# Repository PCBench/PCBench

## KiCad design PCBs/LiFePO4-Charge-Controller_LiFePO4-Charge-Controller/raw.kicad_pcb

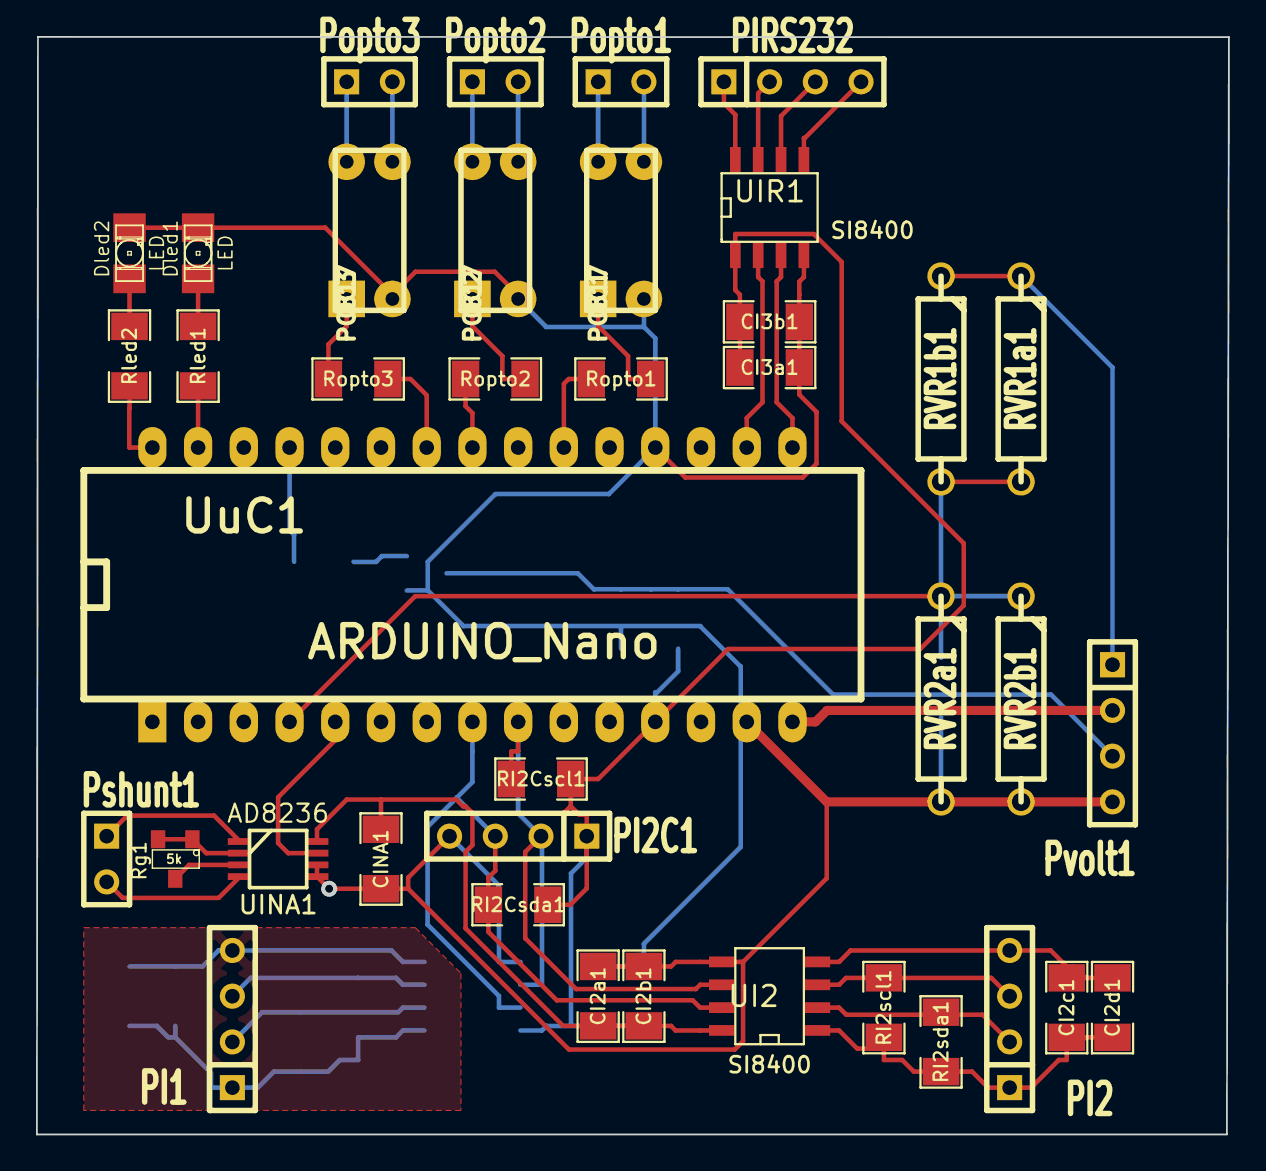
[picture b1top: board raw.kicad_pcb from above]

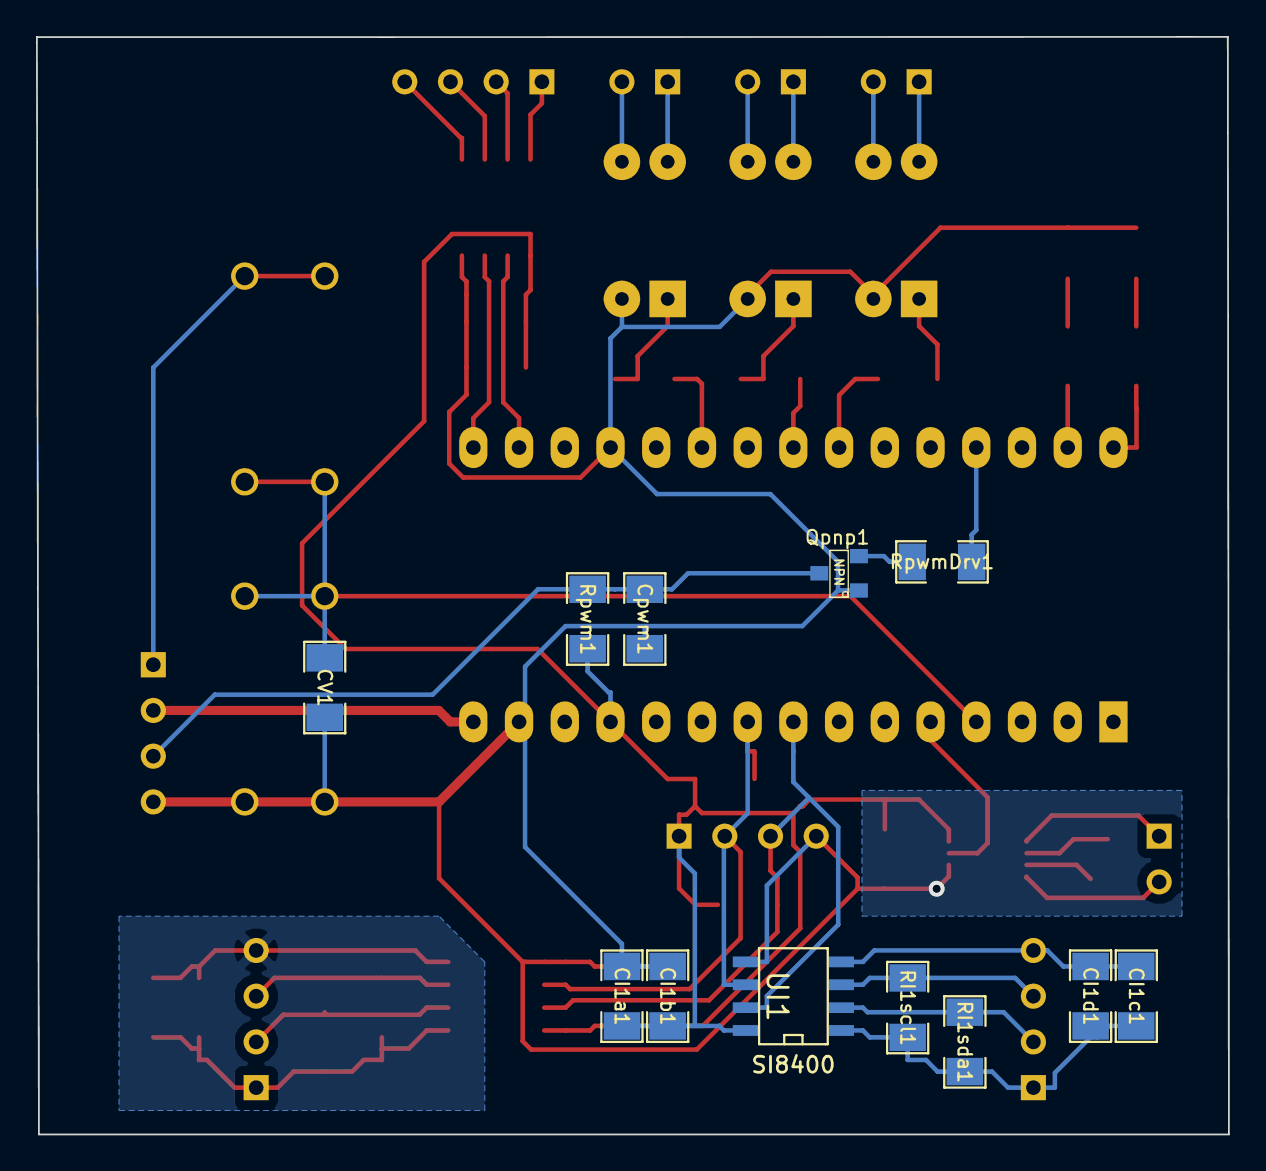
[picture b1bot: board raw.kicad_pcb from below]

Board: 2 copper layers, 66.2 x 61.0 mm, 51 parts (12 on the bottom side), 45 nets.

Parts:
CI1a1, CI1c1, CI2a1, CI2c1, CI3a1: 100nF; SM1206
CI1b1, CI1d1, CI2b1, CI2d1, CI3b1: 1uF; SM1206
CINA1: 100nF; SM1206
CV1: 10pF; SM1206
Cpwm1: 300nF; SM1206
Dled1, Dled2: LED; LED-1206
OC1, OC2, OC3: PC817; DIP-4
PI1, PI2, PI2C1: I2C; SIL-4
PIRS232: RS232; SIL-4
Popto1, Popto2, Popto3: opto; SIL-2
Pshunt1: differential; SIL-2
Pvolt1: Gnd PWM 12V B+; SIL-4
Qpnp1: NPN; SOT23
RI1scl1, RI1sda1, RI2scl1, RI2sda1: 5k; SM1206
RI2Cscl1, RI2Csda1: 1.8k; SM1206
RVR1a1, RVR1b1: 99k; R4-5
RVR2a1, RVR2b1: 1k; R4-5
Rg1: 5k; SOT23
Rled1: 1k; SM1206
Rled2: 1K; SM1206
Ropto1, Ropto2, Ropto3: 1k; SM1206
Rpwm1: 120; SM1206
RpwmDrv1: 560; SM1206
UI1, UI2: SI8400; SO8E
UINA1: AD8236; MSOP_8
UIR1: SI8400; SO8E
UuC1: ARDUINO_Nano; arduino_mini

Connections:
5v: CI1a1.1, CI1b1.1, CI2a1.1, CI2b1.1, CI3a1.2, CI3b1.2, CINA1.1, PI2C1.1, RI2Cscl1.1, RI2Csda1.1, Rpwm1.2, UI1.8, UI2.8, UINA1.8, UIR1.1, UuC1.12
D3: Ropto1.1, UuC1.21
D5: Ropto2.1, UuC1.23
D6: Ropto3.1, UuC1.24
Gnd: CI1a1.2, CI1b1.2, CI2a1.2, CI2b1.2, CI3a1.1, CI3b1.1, CINA1.2, CV1.2, Cpwm1.2, Dled1.2, Dled2.2, OC1.2, OC2.2, OC3.2, PI2C1.4, Pvolt1.4, Qpnp1.1, RVR2a1.2, RVR2b1.2, UI1.5, UI2.5, UINA1.5, UINA1.6, UIR1.4, UuC1.14, UuC1.19
I2C1_GND: CI1c1.2, CI1d1.2, PI1.4, UI1.4
I2C2_GND: CI2c1.2, CI2d1.2, PI2.4, UI2.4
unnamed: UIR1.2, UuC1.17
unnamed: UIR1.3, UuC1.16
unnamed: PI1.3, RI1scl1.2, UI1.3
unnamed: PI1.2, RI1sda1.2, UI1.2
unnamed: PI2.2, RI2sda1.2, UI2.2
unnamed: CV1.1, RVR1a1.2, RVR1b1.2, RVR2a1.1, RVR2b1.1, UuC1.4
unnamed: PIRS232.3, UIR1.6
unnamed: PIRS232.2, UIR1.7
unnamed: PIRS232.1, UIR1.8
unnamed: PI2.3, RI2scl1.2, UI2.3
unnamed: OC1.4, Popto1.1
unnamed: OC3.4, Popto3.1
unnamed: OC3.1, Ropto3.2
unnamed: OC2.3, Popto2.2
unnamed: OC2.4, Popto2.1
unnamed: OC2.1, Ropto2.2
unnamed: OC1.3, Popto1.2
unnamed: OC3.3, Popto3.2
unnamed: OC1.1, Ropto1.2
unnamed: Cpwm1.1, Pvolt1.3, Qpnp1.3, Rpwm1.1
unnamed: Qpnp1.2, RpwmDrv1.2
unnamed: Dled1.1, Rled1.2
unnamed: Dled2.1, Rled2.2
unnamed: RpwmDrv1.1, UuC1.27
unnamed: Rled2.1, UuC1.30
unnamed: Rled1.1, UuC1.29
unnamed: Rg1.1, Rg1.2, UINA1.2
unnamed: UINA1.7, UuC1.5
unnamed: Pshunt1.2, UINA1.4
unnamed: Pshunt1.1, UINA1.1
unnamed: Rg1.3, UINA1.3
unnamed: Pvolt1.2, UuC1.15
unnamed: CI2c1.1, CI2d1.1, PI2.1, RI2scl1.1, RI2sda1.1, UI2.1
unnamed: CI1c1.1, CI1d1.1, PI1.1, RI1scl1.1, RI1sda1.1, UI1.1
unnamed: PI2C1.3, RI2Csda1.2, UI1.7, UI2.7, UuC1.8
unnamed: PI2C1.2, RI2Cscl1.2, UI1.6, UI2.6, UuC1.9
unnamed: Pvolt1.1, RVR1a1.1, RVR1b1.1
RS232_GND: PIRS232.4, UIR1.5

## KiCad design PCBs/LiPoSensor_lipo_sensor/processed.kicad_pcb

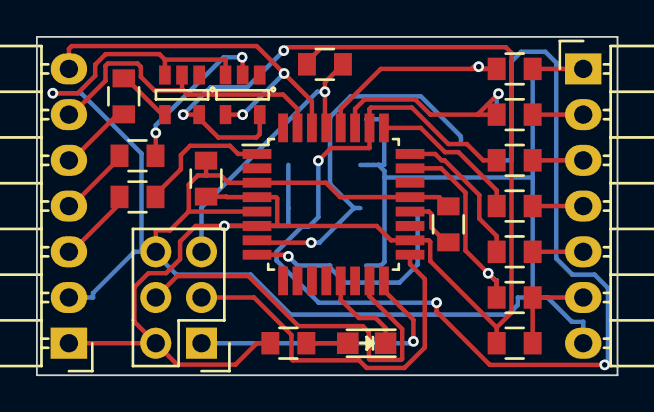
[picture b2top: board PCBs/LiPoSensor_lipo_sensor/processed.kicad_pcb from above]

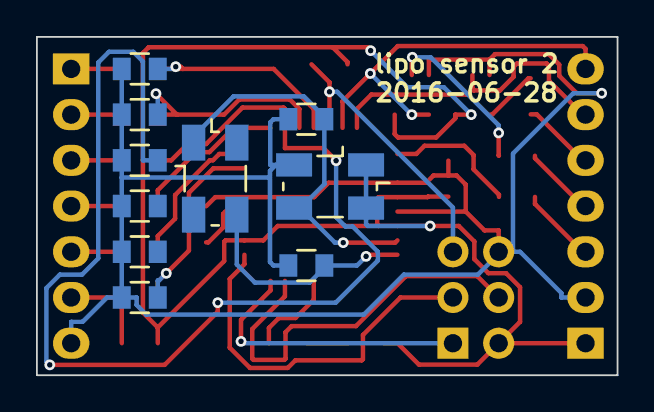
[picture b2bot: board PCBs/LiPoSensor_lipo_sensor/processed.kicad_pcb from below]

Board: 2 copper layers, 32.3 x 18.8 mm, 31 parts (10 on the bottom side), 31 nets.

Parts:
5k1: 4k7; C_0805
C1, C3: 100nF; C_0805
C2, C5: 22pF; C_0805
D1: LED; LED_0805
IC1: ATMEGA328P-A; TQFP-32_7x7mm_Pitch0.8mm
P1: CONN_02X03; Pin_Header_Straight_2x03
P2, P3: CONN_01X07; Pin_Header_Angled_1x07
P4: OSZILLATOR; Oszillator_SMD_5032_4Pads
P5, P6: INVERTER; SOT-23-5
P7: QUARZ; Oszillator_SMD_5032_4Pads
R1: 680; C_0805
R2, R5, R9: 22k; C_0805
R3, R6: 1k; C_0805
R4: 0; C_0805
R7: 18k; C_0805
R8: 1k2; C_0805
R10: 1k8; C_0805
R11: 15k; C_0805
R12: 2k2; C_0805
R13: 12k; C_0805
R14: 3k9; C_0805
R15, R17: R; C_0805
R16: 10k; C_0805

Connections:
/Cell1: IC1.23, R13.2, R14.1
/Cell2: IC1.24, R11.2, R12.1
/Cell3: IC1.25, R9.2, R10.1
/Cell4: IC1.26, R7.2, R8.1
/Cell5: IC1.27, R5.2, R6.1
/Cell6: IC1.28, R2.2, R3.1
/LED: D1.1, IC1.13
/RX: IC1.30, P2.7, P6.4
/S.Port: 5k1.2, IC1.1
/TX: IC1.31, P2.6, P5.2
GND: C1.2, C2.1, C3.1, C5.1, IC1.3, IC1.5, IC1.21, P1.6, P2.2, P3.7, P4.2, P5.3, P6.3, R3.2, R6.2, R8.2, R10.2, R12.2, R14.2
unnamed: 5k1.1, P2.3
unnamed: C2.2, IC1.7, P4.3, P7.1
unnamed: C3.2, IC1.20
unnamed: C5.2, IC1.8, P7.3
unnamed: D1.2, R1.2
unnamed: IC1.15, P1.4
unnamed: IC1.16, P1.1
unnamed: IC1.17, P1.3
unnamed: IC1.29, P1.5, R16.2
unnamed: P2.4, R17.2
unnamed: P2.5, R15.2
unnamed: P3.1, R2.1
unnamed: P3.2, R5.1
unnamed: P3.3, R7.1
unnamed: P3.4, R9.1
unnamed: P3.5, R11.1
unnamed: P3.6, R4.2, R13.1
unnamed: P5.4, R15.1
unnamed: P6.2, R17.1
VCC: C1.1, IC1.4, IC1.6, IC1.18, P1.2, P2.1, P4.1, P4.4, P5.5, P6.5, R1.1, R4.1, R16.1

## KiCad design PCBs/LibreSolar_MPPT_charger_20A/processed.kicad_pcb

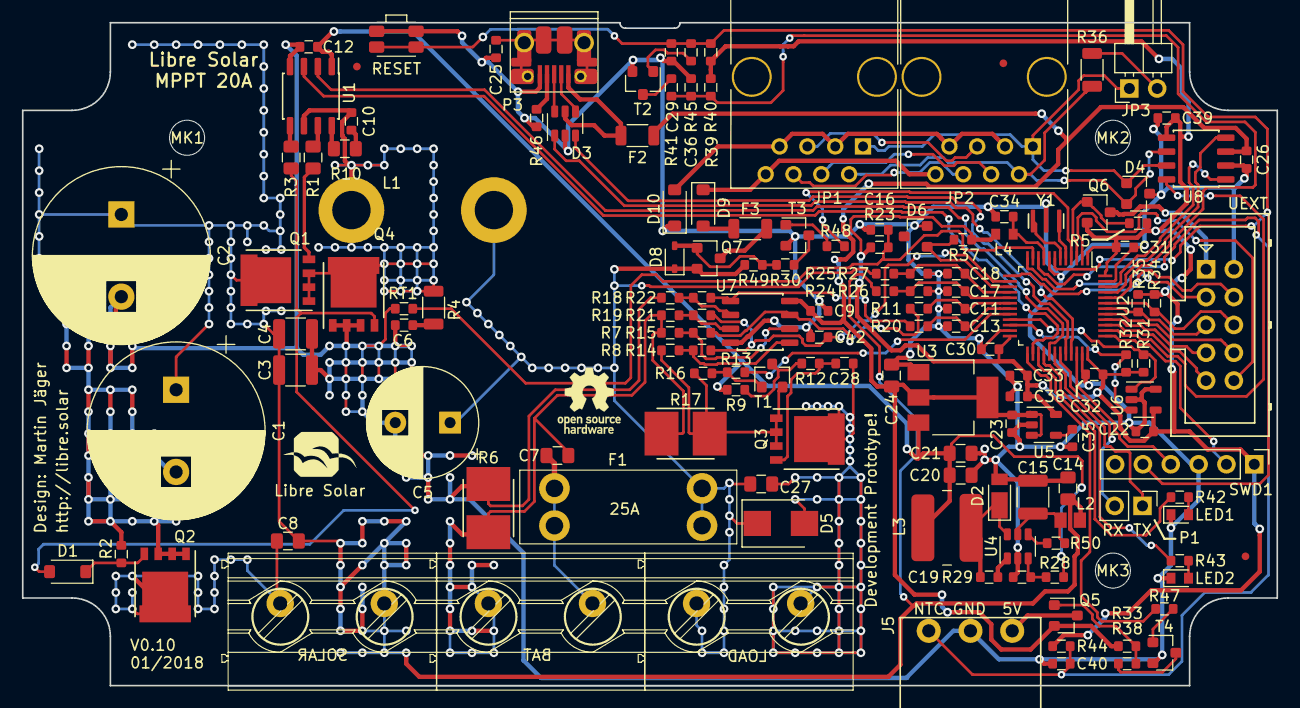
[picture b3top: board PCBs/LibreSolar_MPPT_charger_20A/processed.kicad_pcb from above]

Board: 2 copper layers, 114.5 x 60.5 mm, 146 parts (0 on the bottom side), 102 nets.

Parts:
C1, C2: 1000u; CP_Radial_D16.0mm_P7.50mm
C3, C4, C15: 4.7u; C_1210_3225
C5: 820u; CP_Radial_D10.0mm_P5.00mm
C6: 1n; C_0603_1608
C7, C8, C14, C27: 1u; C_0805_2012
C9, C10, C16, C19, C22, C25, C26, C29, C30, C31, C32, C34, C39, C40, C42: 100n; C_0603_1608
C11, C13, C17, C18, C28: 10n; C_0603_1608
C12, C23, C33, C36, C38: 2.2u; C_0603_1608
C20, C21, C24: 10u; C_0805_2012
C35: 100p; C_0603_1608
D1, D9, D10: 1N4148; D_SOD-123
D2: SS16FP; D_PowerDI-123
D3: USBLC6-2SC6Y; SOT-23-6
D4: NUP2105L; SOT-23
D5: SMBJ36A; D_SMB
D6: LM4040CYM3-2.5; SOT-23
D8: MM3Z12VT1G; D_SOD-323
F1: 25A; KEYSTONE-FUSE-3557-2
F2, F3: 200mA; R_1206_3216
J1: SOLAR; Phoenix_Contact_MKDS_5-2-952
J2: LOAD; Phoenix_Contact_MKDS_5-2-952
J3: BAT; Phoenix_Contact_MKDS_5-2-952
J4: UEXT; Box_Header_2x05x2.54mm_Straight
J5: CONN_01X03; Phoenix_Contact_MC_1,5_3-G-3,81
JP1, JP2: RJ45_NS; RJ45_8P8C
JP3: Jumper_NC_Small; PinHeader_1x02_P2.54mm_Horizontal
L1: 22uH; L-FERYSTER-DTMSS-27
L2: 4.7uH; L_0805_2012Metric
L3: 47uH; Bourns_SRN6045TA
L4: 600R; L_0603_1608Metric
LED1: LED_red; LED_0603_1608Metric
LED2: LED_green; LED_0603_1608Metric
LOGO1: LIBRE_SOLAR; LIBRESOLAR_LOGO
LOGO2: OPEN_HARDWARE; OSHW-Logo_5.7x6mm_SilkScreen
MK1, MK2, MK3: Mounting_Hole; MountingHole_3.2mm_M3
P1: CONN_01X02; PinHeader_1x02_P2.54mm_Vertical
P3: USB Micro B; USB_Micro-B_10103594-0001LF
Q1, Q2, Q3, Q4: CSD18540Q5B; 5X6_MOSFET
Q5, Q6, Q7: BSS84; SOT-23
R1, R3, R10: 3.3; R_0805_2012
R2, R39, R40, R50: 1M; R_0603_1608
R4: 2.2; R_1206_3216
R5, R24, R25, R33, R46, R47: 100k; R_0603_1608
R6, R17: 2m; R_Bourns_CRE2512
R7, R8, R11, R12, R13, R18, R19, R20, R31, R32, R34, R35, R38, R41: 2.2k; R_0603_1608
R9, R30, R45, R49: 56k; R_0603_1608
R14, R15, R21, R22: 150k; R_0603_1608
R16, R23, R27, R29, R37, R44, R48: 10k; R_0603_1608
R26: 5.6k; R_0603_1608
R28: 110k; R_0603_1608
R36: 120; R_1206_3216
R42, R43: 330; R_0603_1608
RT1: 10k; R_0603_1608
SW1: SW_PUSH; SW_SPST_EVQP7A
SWD1: ST_Nucleo_SWD; PinHeader_1x06_P2.54mm_Vertical
T1, T2, T3, T4: MMBT3904; SOT-23
U1: LM5107; SOIC-8_3.9x4.9mm_Pitch1.27mm
U2: STM32F072CB; LQFP-48_7x7mm_P0.5mm
U3: AZ1117; SOT-223-3_TabPin2
U4: MP2459; SOT-23-6
U5: AP2210-3.3; SOT-23-5
U6: 24AA01; SOT-23-5
U7: LM258; SOIC-8_3.9x4.9mm_Pitch1.27mm
U8: TJA1042T/3; SOIC-8_3.9x4.9mm_Pitch1.27mm
Y1: 8MHz; Resonator_Murata_CSTCE_G

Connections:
+3V3: C22.1, C30.1, C31.1, C32.1, C33.1, C38.1, C39.1, L4.1, Q6.2, R5.1, R23.1, R31.2, R32.2, R34.2, R35.2, R37.2, R39.2, R40.2, R44.1, SWD1.1, U2.1, U2.24, U2.36, U2.48, U5.5, U6.4, U8.5
+5V: C9.1, C23.1, C24.1, C26.1, F2.1, Q5.2, R33.1, U3.2, U5.1, U5.3, U7.8, U8.3
+10V: C12.1, C20.1, C21.1, L3.2, R9.2, R28.1, U1.1, U3.3
/Analog Frontend/TEMP_BAT: C40.1, J5.1, R44.2, U2.10
/Analog Frontend/TEMP_INT: C16.1, R23.2, RT1.1, U2.11
/Communication Interfaces/5V_OUT: J5.3, Q5.3
/Communication Interfaces/5V_OUT_EN: R47.2, U2.25
/Communication Interfaces/CAN_GND: D10.2, JP1.3, JP1.7, JP2.3, JP2.7
/Communication Interfaces/CAN_H: D4.1, JP1.1, JP2.1, JP3.1, U8.7
/Communication Interfaces/CAN_L: D4.2, JP1.2, JP2.2, R36.2, U8.6
/Communication Interfaces/CAN_RX: U2.45, U8.4
/Communication Interfaces/CAN_SHLD: JP1.6, JP2.6
/Communication Interfaces/CAN_STB: U2.38, U8.8
/Communication Interfaces/CAN_TX: U2.46, U8.1
/Communication Interfaces/CAN_V+: D9.1, JP1.8, JP2.8
/Communication Interfaces/RJ45_4: JP1.4, JP2.4
/Communication Interfaces/RJ45_5: JP1.5, JP2.5
/Communication Interfaces/UEXT_EN: Q6.1, R5.2, U2.3
/Communication Interfaces/UEXT_RX: J4.4, U2.13
/Communication Interfaces/UEXT_TX: J4.3, U2.12
/Communication Interfaces/USB_DM: D3.3, U2.32
/Communication Interfaces/USB_DP: D3.1, U2.33
/Communication Interfaces/V_BUS_EN: R48.2, U2.4
/DCDC power stage/BAT+: C7.1, F1.2, J3.2
/DCDC power stage/BAT-: C7.2, J3.1, R6.2, R7.2, R17.1, R19.2
/DCDC power stage/DCDC_IN: C1.1, C2.1, C3.1, C4.1, C8.1, C14.1, J1.2, L2.1, Q1.D, R24.1
/DCDC power stage/HS_DRV: R1.2, U1.7
/DCDC power stage/LOAD-: C27.2, C28.2, D5.2, J2.2, Q3.D
/DCDC power stage/LOAD-SW: Q3.S, R8.2, R16.1, R17.2, T1.2
/DCDC power stage/LS_DRV: R3.2, U1.5
/DCDC power stage/PWM_HS: U1.2, U2.29
/DCDC power stage/PWM_LS: U1.3, U2.26
/DCDC power stage/SOLAR-: C8.2, J1.1, Q2.D
/DCDC power stage/SW_NODE: C10.2, L1.1, Q1.S, Q4.D, R4.2, U1.6
/DCDC power stage/~LOAD_EN: R13.2, U2.20
/DCDC_OUT: C5.1, C27.1, D5.1, D8.1, F1.1, J2.1, L1.2, Q7.2, R25.1, R49.1
/MCU/BOOT0: C36.1, R39.1, R41.2, U2.44
/MCU/DAC: C42.1, R14.1, R21.2, U2.14
/MCU/I2C1_SCL: J4.5, R35.1, U2.42
/MCU/I2C1_SDA: J4.6, R34.1, U2.43
/MCU/I2C2_SCL: R31.1, U2.21, U6.1
/MCU/I2C2_SDA: R32.1, U2.22, U6.3
/MCU/I_DCDC: C13.1, R20.2, U2.19
/MCU/I_LOAD: C11.1, R11.2, U2.18
/MCU/LED1: R42.2, U2.27
/MCU/LED2: R43.2, U2.28
/MCU/OSC_IN: U2.5, Y1.1
/MCU/OSC_OUT: U2.6, Y1.3
/MCU/SPI1_MISO: J4.7, U2.40
/MCU/SPI1_MOSI: J4.8, U2.41
/MCU/SPI1_SCK: J4.9, U2.39
/MCU/SSEL: J4.10, U2.2
/MCU/SWCLK: SWD1.2, U2.37
/MCU/SWDIO: SWD1.4, U2.34
/MCU/USART1_RX: P1.2, U2.31
/MCU/USART1_TX: P1.1, U2.30
/MCU/V_BAT: C18.1, R25.2, R27.1, U2.16
/MCU/V_REF: D6.1, R37.1, U2.15
/MCU/V_SOLAR: C17.1, R24.2, R26.1, U2.17
/MCU/~RESET: C29.1, R40.1, R45.1, SW1.1, SWD1.5, U2.7
GND: C1.2, C2.2, C3.2, C4.2, C5.2, C6.2, C9.2, C11.2, C12.2, C13.2, C14.2, C15.2, C16.2, C17.2, C18.2, C20.2, C21.2, C22.2, C23.2, C24.2, C25.2, C26.2, C29.2, C30.2, C31.2, C32.2, C33.2, C34.2, C35.2, C36.2, C38.2, C39.2, C40.2, C42.2, D2.2, D3.2, D4.3, D6.2, D10.1, J4.2, J5.2, LED1.1, LED2.1, P3.5, Q2.S, Q4.S, R2.1, R6.1, R18.2, R26.2, R27.2, R29.2, R46.2, RT1.2, SW1.2, SWD1.3, T2.2, T3.2, T4.2, U1.4, U2.8, U2.23, U2.35, U2.47, U3.1, U4.2, U5.2, U6.2, U6.5, U7.4, U8.2, Y1.2
unnamed: C6.1, R4.1
unnamed: C10.1, R10.1
unnamed: C15.1, L2.2, R50.2, U4.5
unnamed: C19.1, U4.1
unnamed: C19.2, D2.1, L3.1, U4.6
unnamed: C25.1, P3.6
unnamed: C28.1, Q3.G, R12.1
unnamed: C34.1, L4.2, U2.9
unnamed: C35.1, U5.4
unnamed: D1.1, Q2.G, R2.2
unnamed: D1.2, Q4.G, R3.1
unnamed: D3.4, P3.2
unnamed: D3.5, F2.2, P3.1
unnamed: D3.6, P3.3
unnamed: D8.2, Q7.1, R30.1, R49.2
unnamed: D9.2, F3.1
unnamed: F3.2, Q7.3
unnamed: J4.1, Q6.3
unnamed: JP3.2, R36.1
unnamed: LED1.2, R42.1
unnamed: LED2.2, R43.1
unnamed: P3.4, R46.1
unnamed: Q1.G, R1.1
unnamed: Q5.1, R33.2, R38.1
unnamed: R10.2, U1.8
unnamed: R11.1, R15.2, U7.7
unnamed: R9.1, R12.2, T1.3
unnamed: R13.1, R16.2, T1.1
unnamed: R8.1, R14.2, U7.5
unnamed: R7.1, R15.1, U7.6
unnamed: R18.1, R22.1, U7.2
unnamed: R19.1, R21.1, U7.3
unnamed: R20.1, R22.2, U7.1
unnamed: R28.2, R29.1, U4.3
unnamed: R30.2, T3.3
unnamed: R38.2, T4.3
unnamed: R41.1, T2.3
unnamed: R45.2, T2.1
unnamed: R47.1, T4.1
unnamed: R48.1, T3.1
unnamed: R50.1, U4.4

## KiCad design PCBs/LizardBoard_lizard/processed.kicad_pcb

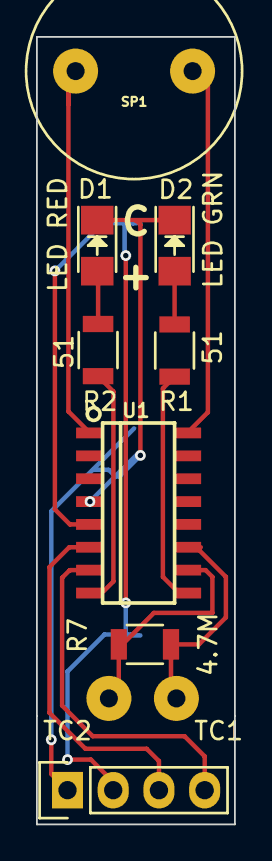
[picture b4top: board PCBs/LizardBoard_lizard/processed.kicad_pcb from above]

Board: 2 copper layers, 11.0 x 43.8 mm, 11 parts (1 on the bottom side), 12 nets.

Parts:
BT1: BATTERY; linx-bat-hld-001
C4: TC1; SolderWirePad_single_1mmDrill
C5: TC2; SolderWirePad_single_1mmDrill
D1: LED RED; LED-1206
D2: LED GRN; LED-1206
P1: DEBUG; Pin_Header_Straight_1x04
R1, R2: 51; R_1206
R7: 4.7M; R_1206
SP1: SPEAKER; PUI-AT-1224-TWT-5V-2-R
U1: EFM8BB1; soic16

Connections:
GND: BT1.2, D1.1, D2.1, P1.1, U1.4
unnamed: C4.1, R7.1, U1.11
unnamed: C5.1, R7.2, U1.10
unnamed: D1.2, R2.1
unnamed: D2.2, R1.1
unnamed: P1.3, U1.6
unnamed: P1.4, U1.7
unnamed: R1.2, U1.9
unnamed: R2.2, U1.8
unnamed: SP1.1, U1.16
unnamed: SP1.2, U1.1
VDD: BT1.1, P1.2, U1.5

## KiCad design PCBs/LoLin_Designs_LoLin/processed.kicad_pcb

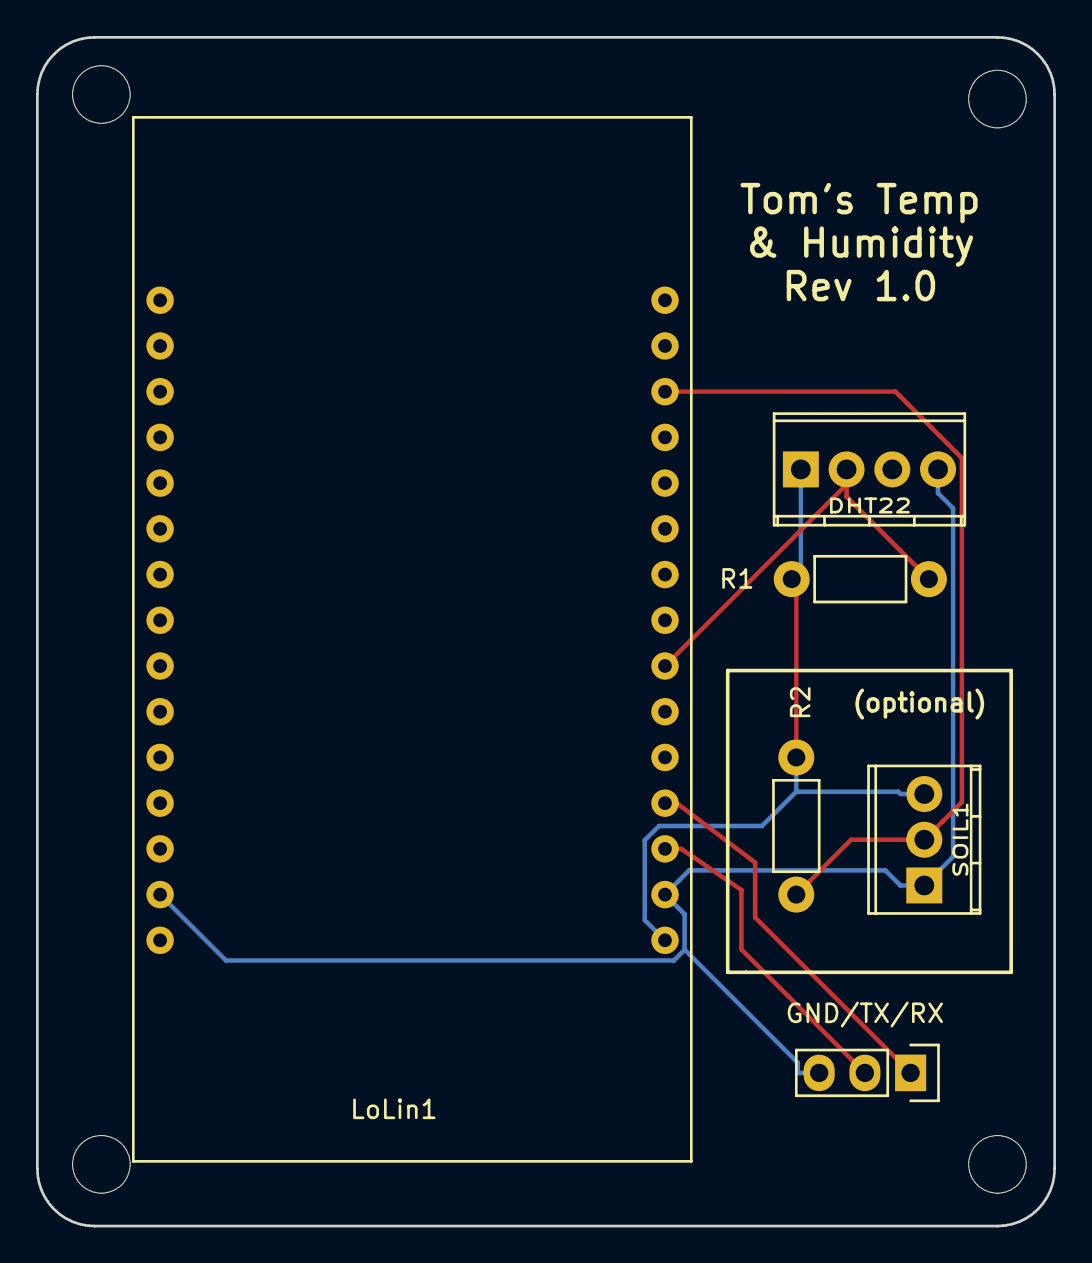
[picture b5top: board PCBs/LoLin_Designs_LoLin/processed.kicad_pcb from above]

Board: 2 copper layers, 56.5 x 66.0 mm, 6 parts (0 on the bottom side), 6 nets.

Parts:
DHT22: DHT22; TerminalBlock_Pheonix_MPT-2.54mm_4pol
GND/TX/RX: RX/TX/GND; Pin_Header_Straight_1x03
LoLin1: LoLin_V3; LoLin
R1, R2: 4.7K; Resistor_Horizontal_RM7mm
SOIL1: SOIL; TerminalBlock_Pheonix_MPT-2.54mm_3pol

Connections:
3.3V: DHT22.1, LoLin1.16, R1.1, R2.2, SOIL1.3
GND: DHT22.4, GND/TX/RX.3, LoLin1.14, LoLin1.17, SOIL1.1
unnamed: GND/TX/RX.1, LoLin1.19
unnamed: GND/TX/RX.2, LoLin1.18
SOIL_TEMP: LoLin1.28, R2.1, SOIL1.2
TEMP_READING: DHT22.2, LoLin1.22, R1.2

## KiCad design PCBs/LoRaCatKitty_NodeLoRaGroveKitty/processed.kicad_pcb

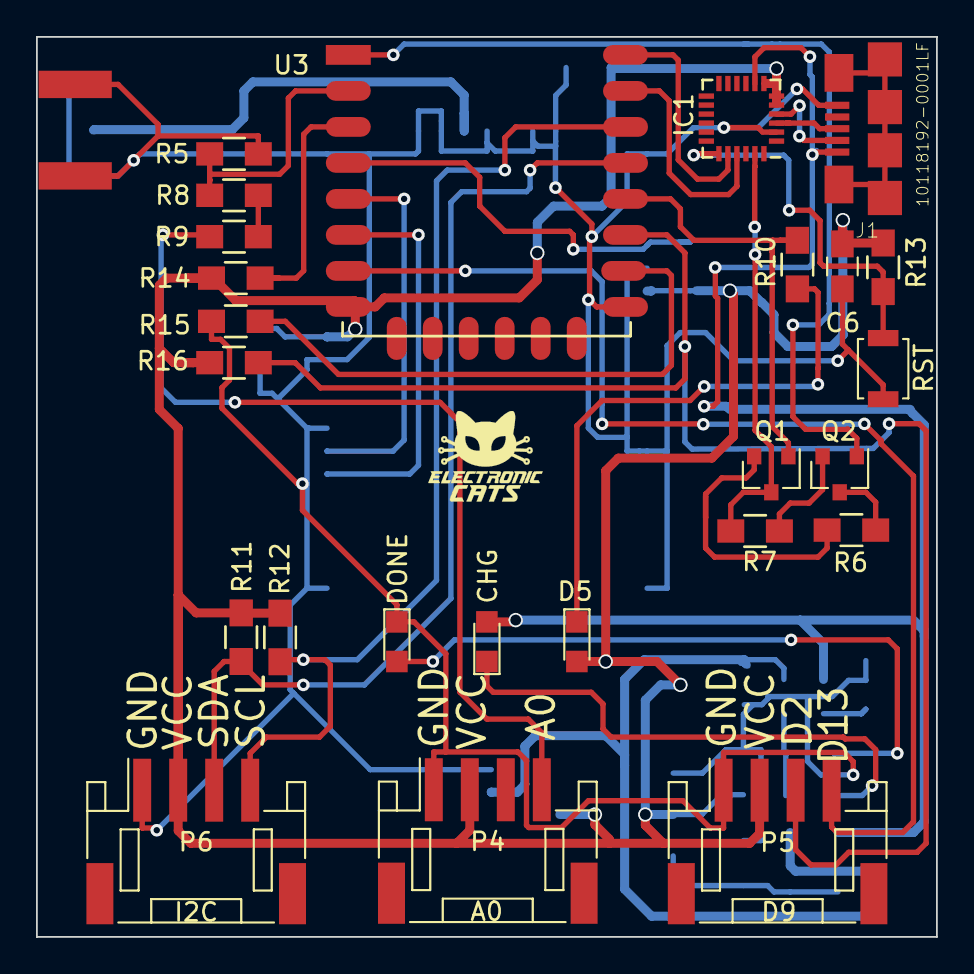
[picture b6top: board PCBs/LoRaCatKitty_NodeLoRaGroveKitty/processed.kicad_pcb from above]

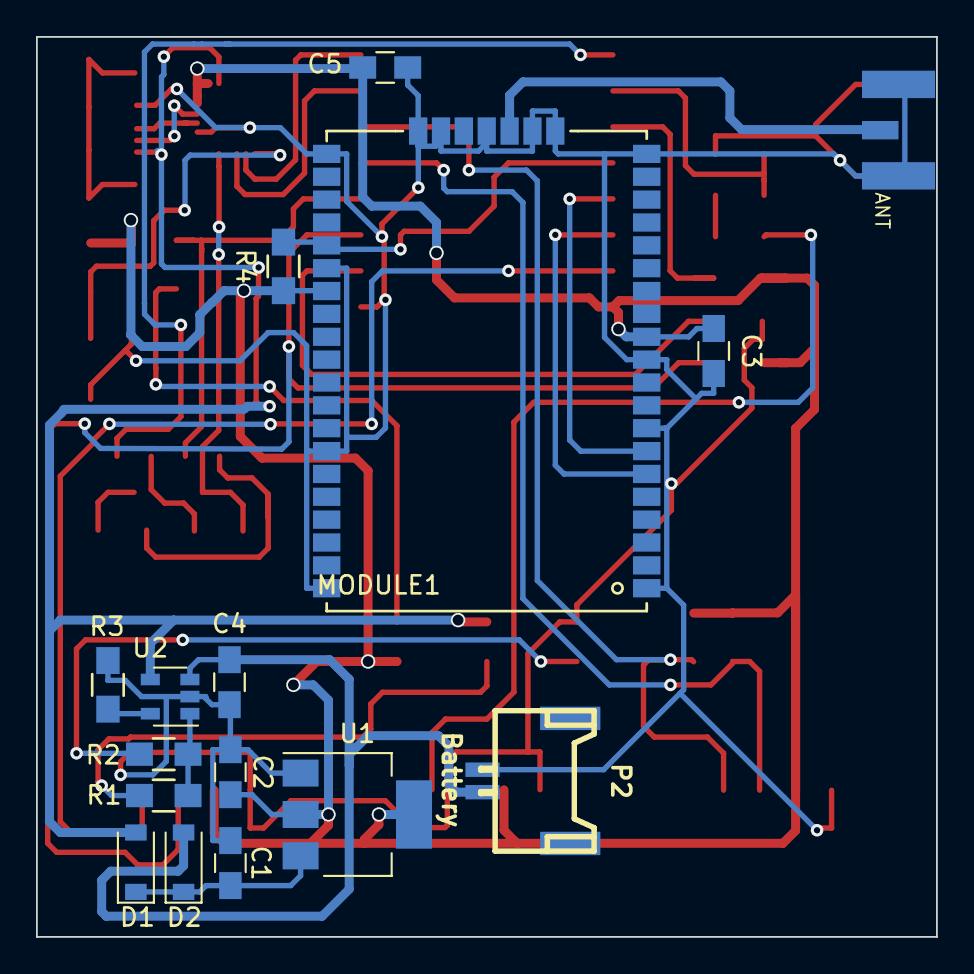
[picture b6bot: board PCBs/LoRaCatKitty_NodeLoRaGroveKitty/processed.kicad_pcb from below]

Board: 2 copper layers, 50.0 x 50.0 mm, 41 parts (16 on the bottom side), 35 nets.

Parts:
A1: ANT; SMA_Conn_Ant
C1, C2: 4.7uF; C_0805_HandSoldering
C3, C5: 0.1uF; C_0805_HandSoldering
C4, C6: 10uF; C_0805_HandSoldering
D1, D2: MBR120; D_SOD-123
D3: CHG; LED_0805
D4: DONE; LED_0805
D5: Led; LED_0805
IC1: CP2104; QFN-24_4x4mm_Pitch0.5mm_NoMask
J1: 10118192-0001LF
MODULE1: RN2903; RN2483
P2: Battery; panelmate_smd_2
P4: A0; JST_PH_S4B-PH-SM4-TB_04x2.00mm_Angled
P5: D9; JST_PH_S4B-PH-SM4-TB_04x2.00mm_Angled
P6: I2C; JST_PH_S4B-PH-SM4-TB_04x2.00mm_Angled
Q1, Q2: MMBT2222A; SOT-23
R1, R2, R10: 330R; R_0805_HandSoldering
R3, R4, R6, R7, R13, R14, R15, R16: 10K; R_0805_HandSoldering
R5, R8, R9: 100K; R_0805_HandSoldering
R11, R12: 4.7K; R_0805_HandSoldering
RST: SW_RESET; SW_SPST_B3U-1000P
U1: AP2114; SOT-223-3Lead_TabPin2
U2: MCP73831T-2ATI/OT; SOT-23-5
U3: ESP8266-12E; ESP-12E

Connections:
+3V3: C2.1, C3.1, C5.1, C6.1, D5.2, IC1.5, IC1.6, IC1.7, MODULE1.12, MODULE1.34, P4.2, P5.2, P6.2, R4.1, R11.1, R12.1, R13.1, R14.1, R16.1, U1.2, U3.8
+BATT: C4.1, D2.2, P2.1, U2.3
/A0: P4.4, R9.1
/ADC: R5.1, R8.2, U3.2
/CH_PD: R14.2, U3.3
/DTR: IC1.23, Q1.3, R7.2
/GPIO0: Q1.1, R10.1, U3.12
/GPIO2: P5.3, R16.2, U3.11
/GPIO13: P5.4, U3.7
/GPIO15: R15.1, U3.10
/RESET: Q2.1, U3.1
/RST: IC1.19, R13.2, RST.2
/RST_RN: MODULE1.32, R4.2, U3.4
/RTS: Q2.3, R6.2
/RXD: IC1.21, U3.15
/SCL: P6.4, R12.2, U3.14
/SDA: P6.3, R11.2, U3.13
/SRX: MODULE1.6, U3.6
/STX: MODULE1.7, U3.5
/TXD: IC1.20, U3.16
GND: A1.2, A1.3, A1.4, A1.5, C1.2, C2.2, C3.2, C4.2, C5.2, C6.2, D4.1, IC1.2, J1.5, MODULE1.1, MODULE1.8, MODULE1.11, MODULE1.20, MODULE1.21, MODULE1.22, MODULE1.24, MODULE1.26, MODULE1.27, MODULE1.28, MODULE1.33, MODULE1.41, MODULE1.47, P2.2, P4.1, P5.1, P6.1, R3.2, R5.2, R15.2, RST.1, U1.1, U2.2, U3.9
unnamed: A1.1, MODULE1.23
unnamed: C1.1, D1.1, D2.1, U1.3
unnamed: D3.1, R1.2
unnamed: D4.2, R2.2
unnamed: D5.1, R10.2
unnamed: IC1.3, J1.3
unnamed: IC1.4, J1.2
unnamed: J1.M1, J1.M2, J1.S1, J1.S2, J1.S3, J1.S4
unnamed: Q1.2, R6.1
unnamed: Q2.2, R7.1
unnamed: R1.1, R2.1, U2.1
unnamed: R3.1, U2.5
unnamed: R8.1, R9.2
VCC: D1.2, D3.2, IC1.8, J1.1, U2.4

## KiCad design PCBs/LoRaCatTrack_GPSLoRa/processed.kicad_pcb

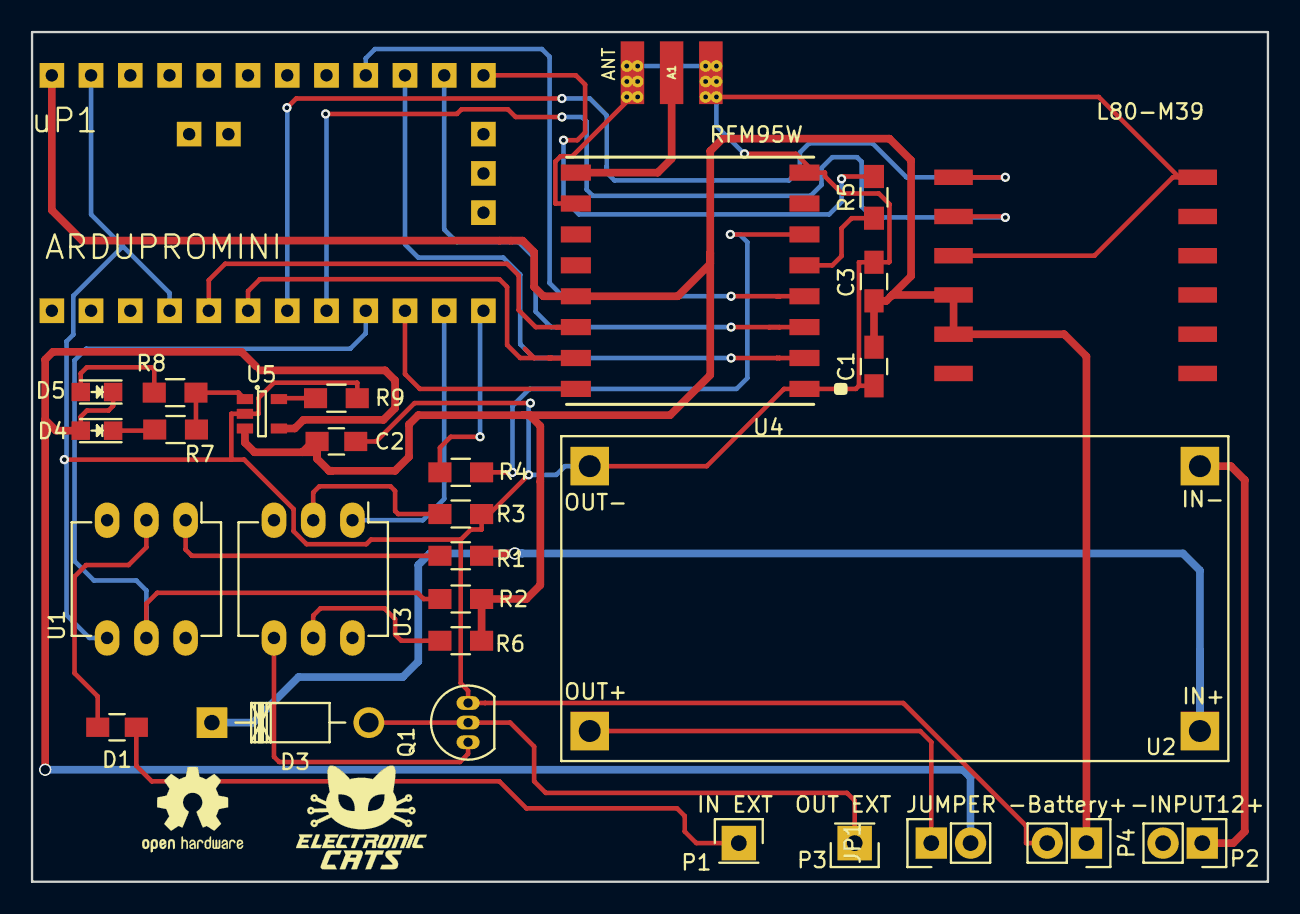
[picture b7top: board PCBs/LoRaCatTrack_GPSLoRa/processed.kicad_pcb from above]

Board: 2 copper layers, 80.0 x 55.0 mm, 30 parts (0 on the bottom side), 32 nets.

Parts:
A1: ANT; GSG-SMA-EDGE
C1, C3: 0.1uF; C_0805_HandSoldering
C2: 10uF; C_0805_HandSoldering
D1: D; C_0805_HandSoldering
D3: D; Diode_DO-41_SOD81_Horizontal_RM10
D4, D5: LED; LED_0805
JP1: JUMPER; Pin_Header_Straight_1x02
MODULE1: L80-M39; QUECTEL_L80-M39
P1: IN EXT; Pin_Header_Straight_1x01
P2: -INPUT12+; Pin_Header_Straight_1x02
P3: OUT EXT; Pin_Header_Straight_1x01
P4: -Battery+; Pin_Header_Straight_1x02
Q1: Q_NPN_BCE; TO-92_Inline_Narrow_Oval
R1, R6, R9: 1K; R_0805_HandSoldering
R2, R4, R5: 10K; R_0805_HandSoldering
R3, R7, R8: 220R; R_0805_HandSoldering
U1, U3: 4N26; DIP-6_W7.62mm_LongPads
U2: LM2596_Breakout; LM2596DC-DC
U4: RFM95W; XCVR_RFM95W-868S2
U5: MCP73831T-2ATI/OT; SOT-23-5
uP1: ARDUPROMINI; arduinoMiniPro2

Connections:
+5V: D4.2, D5.1, JP1.2, U5.4
+12C: D3.1, R1.1, U2.1
+BATT: C1.1, C2.1, C3.1, MODULE1.4, MODULE1.5, P4.1, R2.1, R6.1, U4.13, U5.3, uP1.19
/D6: R2.2, U1.5, uP1.15
/D8: U3.1, uP1.17
/DIO0: U4.14, uP1.11
/DIO1: U4.15, uP1.12
/DIO2: U4.16, uP1.16
/MISO: U4.2, uP1.28
/MOSI: U4.3, uP1.29
/NSS: R5.1, uP1.30
/RST: R4.1, uP1.18
/RX: MODULE1.2, uP1.14
/SCK: U4.4, uP1.27
/TX: MODULE1.1, uP1.13
GND: A1.2, A1.3, A1.4, A1.5, C1.2, C2.2, C3.2, MODULE1.3, MODULE1.12, P4.2, Q1.3, R3.2, R9.2, U1.4, U2.4, U4.1, U4.8, U4.10, U5.2, uP1.10, uP1.20
unnamed: A1.1, U4.9
unnamed: D1.1, P1.1
unnamed: D1.2, U1.2
unnamed: D3.2, P3.1, Q1.2
unnamed: D4.1, R7.2
unnamed: D5.2, R8.2
unnamed: JP1.1, U2.3
unnamed: P2.1, U2.2
unnamed: Q1.1, U3.4
unnamed: R1.2, U1.1
unnamed: R3.1, U3.2
unnamed: R4.2, U4.6
unnamed: R5.2, U4.5
unnamed: R6.2, U3.5
unnamed: R7.1, R8.1, U5.1
unnamed: R9.1, U5.5

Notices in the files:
PCBs/LizardBoard_lizard/processed.kicad_pcb:
Copyright © 2015 Bart Massey
Open Hardware: see repo for license terms
